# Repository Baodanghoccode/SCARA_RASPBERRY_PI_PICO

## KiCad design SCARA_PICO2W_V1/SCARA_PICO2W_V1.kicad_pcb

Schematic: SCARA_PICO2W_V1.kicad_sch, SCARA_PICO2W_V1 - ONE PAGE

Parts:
A201: Raspberry Pi Pico 2 W; RaspberryPi_Pico_Common_THT_AntennaWindow; MPN Raspberry Pi Pico 2 W
A401, A501, A601, A701: A4988 module; Pololu_Breakout-16_15.2x20.3mm_Socket_D1.02mm; MPN Nshop 6R08 A4988 module
C101: 470u 50V; CP_Radial_D12.5mm_P5.00mm; Voltage 50V; Tolerance 20%; MPN UPW1H471MHD
C102, C402, C502, C602, C702: 100n 50V; C_0805_2012Metric; Tolerance 10%; Voltage 50 V; MPN CC0805KRX7R9BB104
C103: 470u 25V LOW ESR; CP_Radial_D10.0mm_P5.00mm; MPN UPW1E471MPD
C104: 330u 35V LOW ESR; CP_Radial_D10.0mm_P5.00mm; MPN UPW1V331MPD
C105, C120, C121: 470u 50V LOW ESR; CP_Radial_D12.5mm_P5.00mm; MPN UPW1H471MHD
C106: 100n 50V X7R; C_0805_2012Metric; MPN 0805 100nF50V X7R +/-10%
C112: 10n 50V X7R; C_0805_2012Metric; MPN 0805 10nF50V X7R +/-10%
C122, C124, C125: 1u 50V X7R; C_0805_2012Metric; MPN 0805 1uF50V X7R +/-10%
C132: 27n 50V X7R; C_0805_2012Metric; MPN 0805 27nF50V X7R +/-10%
C401, C501, C601, C701: 100u 50V; CP_Radial_D8.0mm_P3.50mm; Voltage 50V; Tolerance 20%; MPN UPW1H101MPD
C403, C503, C603, C703, C801, C901, C902, C903, C904, C905: 100n 16V; C_0805_2012Metric; Tolerance 10%; Voltage 50 V; MPN CC0805KRX7R9BB104
C802, C803: 220u 25V; CP_Radial_D8.0mm_P3.50mm; MPN EEUFR1E221
D102: 1.5KE30CA / DNP; D_DO-201AD_P15.24mm_Horizontal; MPN 1.5KE30CA; not fitted
D103, D104: MBR20100CT; TO-220-3_Vertical; MPN MBR20100CT (manufacturer/lot verify)
D151: BZT52C12; D_SOD-123; MPN BZT52C12
D201: SS14-E3/61T; D_SMA; MPN SS14-E3/61T
F101: 6.3A / 125VDC; Fuse_Littelfuse-NANO2-451_453; MPN 045106.3MRL
J101: 24V IN; TerminalBlock_Phoenix_MKDS-1,5-2-5.08_1x02_P5.08mm_Horizont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; MPN 1715721
J201: EXPANSION; PinHeader_1x10_P2.54mm_Vertical; MPN M20-9991046
J401: AX1 MOTOR; PinHeader_1x04_P2.54mm_Vertical; MPN M20-9990446
J501: AX2 MOTOR; PinHeader_1x04_P2.54mm_Vertical; MPN M20-9990446
J601: AX3 MOTOR; PinHeader_1x04_P2.54mm_Vertical; MPN M20-9990446
J701: AX4 MOTOR; PinHeader_1x04_P2.54mm_Vertical; MPN M20-9990446
J801: SERVO1 MG996R; PinHeader_1x03_P2.54mm_Vertical; MPN M20-9990346
J802: SERVO2 MG996R; PinHeader_1x03_P2.54mm_Vertical; MPN M20-9990346
J901: HOME1 NC; JST_XH_B2B-XH-A_1x02_P2.50mm_Vertical; MPN B2B-XH-A(LF)(SN)
J902: HOME2 NC; JST_XH_B2B-XH-A_1x02_P2.50mm_Vertical; MPN B2B-XH-A(LF)(SN)
J903: HOME3 NC; JST_XH_B2B-XH-A_1x02_P2.50mm_Vertical; MPN B2B-XH-A(LF)(SN)
J904: HOME4 NC; JST_XH_B2B-XH-A_1x02_P2.50mm_Vertical; MPN B2B-XH-A(LF)(SN)
J905: STOP_SENSE NC; JST_XH_B2B-XH-A_1x02_P2.50mm_Vertical; MPN B2B-XH-A(LF)(SN)
JP401, JP501, JP601, JP701: MS1 OPEN=0; PinHeader_1x02_P2.54mm_Vertical; MPN M20-9990246
JP402, JP502, JP602, JP702: MS2 OPEN=0; PinHeader_1x02_P2.54mm_Vertical; MPN M20-9990246
JP403, JP503, JP603, JP703: MS3 OPEN=0; PinHeader_1x02_P2.54mm_Vertical; MPN M20-9990246
JP801: SERVO ARM (OPEN); PinHeader_1x02_P2.54mm_Vertical; MPN M20-9990246
L101: 100u / CDRH127; L_12x12mm_H8mm; MPN CDRH127-101 (local part; exact manufact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
L102: 47u / CXT B011307; L_Toroid_Vertical_D20_W10_P10_Wire1mm; MPN CXT B011307 (47uH 10A advertised)
Q151: IRF4905; TO-220-3_Vertical_Drill1.4mm; MPN IRF4905PbF
R105, R123: 3k3 1%; R_0805_2012Metric; MPN 0805 3k3 1% >=0.125W
R106: 1k 1%; R_0805_2012Metric; MPN 0805 1k 1% >=0.125W
R107: 75R 1%; R_0805_2012Metric; MPN 0805 75R 1% >=0.125W
R122: 12k 1%; R_0805_2012Metric; MPN 0805 12k 1% >=0.125W
R124: 560R 1%; R_0805_2012Metric; MPN 0805 560R 1% >=0.125W
R150: 2k2 1% / 0.25W; R_0805_2012Metric; MPN 0805 2.2k 1% 0.25W
R151: 100k 1%; R_0805_2012Metric; MPN 0805 100k 1%
R401, R402, R403, R404, R405, R406, R407, R501, R502, R503, R504, R505, R506, R507, R601, R602, R603, R604, R605, R606, R607, R701, R702, R703, R704, R705, R706, R707, R801, R802, R807: 10k; R_0805_2012Metric; Tolerance 1%; MPN RC0805FR-0710KL
R803, R804: 220R; R_0805_2012Metric; Tolerance 1%; MPN RC0805FR-07220RL
R805, R806: 100k; R_0805_2012Metric; Tolerance 1%; MPN RC0805FR-07100KL
R901, R903, R905, R907, R909: 4k7; R_0805_2012Metric; Tolerance 1%; MPN RC0805FR-074K7L
R902, R904, R906, R908, R910: 1k; R_0805_2012Metric; Tolerance 1%; MPN RC0805FR-071KL
TP101: +24V_MAIN; TestPoint_Pad_D2.0mm; MPN PCB_PAD_2MM_NO_ASSEMBLY
TP102: +5V_LOGIC; TestPoint_Pad_D2.0mm; MPN PCB_PAD_2MM_NO_ASSEMBLY
TP103: +6V_SERVO; TestPoint_Pad_D2.0mm; MPN PCB_PAD_2MM_NO_ASSEMBLY
TP104: VSYS; TestPoint_Pad_D2.0mm; MPN PCB_PAD_2MM_NO_ASSEMBLY
TP105: +3V3; TestPoint_Pad_D2.0mm; MPN PCB_PAD_2MM_NO_ASSEMBLY
TP106: GND; TestPoint_Pad_D2.0mm; MPN PCB_PAD_2MM_NO_ASSEMBLY
U101: LM2596S-ADJ; TO-263-5_TabPin3; MPN LM2596S-ADJ (manufacturer/lot verify)
U102: XL4015E1; TO-263-5_TabPin3; MPN XL4015E1
U801: SN74AHCT125PWR; TSSOP-14_4.4x5mm_P0.65mm; MPN SN74AHCT125PWR

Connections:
+3V3: A201.36 (3V3), A401.2 (VDD), A501.2 (VDD), A601.2 (VDD), A701.2 (VDD), C403.1, C503.1, C603.1, C703.1, J201.8, JP401.1, JP402.1, JP403.1, JP501.1, JP502.1, JP503.1, JP601.1, JP602.1, JP603.1, JP701.1, JP702.1, JP703.1, R403.1, R404.1, R503.1, R504.1, R603.1, R604.1, R703.1, R704.1, R901.1, R903.1, R905.1, R907.1, R909.1, TP105.1 (1_1)
+5V_LOGIC: C103.1, C112.1, C801.1, D201.2 (A), L101.2, R105.1, R807.1, TP102.1 (1_1), U801.10, U801.13, U801.14 (VCC)
+6V_SERVO: C104.1, C125.1, C132.1, C802.1, C803.1, J801.2, J802.2, L102.2, R122.1, TP103.1 (1_1)
+24V_MAIN: A401.8 (VMOT), A501.8 (VMOT), A601.8 (VMOT), A701.8 (VMOT), C101.1, C102.1, C105.1, C106.1, C120.1, C121.1, C122.1, C124.1, C401.1, C402.1, C501.1, C502.1, C601.1, C602.1, C701.1, C702.1, D102.1 (A1), D151.1 (K), Q151.3 (S), R151.1, TP101.1 (1_1), U101.1 (VIN), U102.5 (VIN)
/BUCK5_FB: C112.2, R105.2, R106.1, U101.4 (FB)
/BUCK5_SW: D103.2 (K), L101.1, U101.2 (OUT)
/BUCK6_FB: C132.2, R123.1, R124.2, U102.2 (FB)
/BUCK6_SW: D104.2 (K), L102.1, U102.3 (SW)
/RP_GATE: D151.2 (A), Q151.1 (G), R150.1, R151.2
AX1_1A: A401.4 (1A), J401.3
AX1_1B: A401.3 (1B), J401.4
AX1_2A: A401.5 (2A), J401.2
AX1_2B: A401.6 (2B), J401.1
AX1_DIR: A201.5 (GPIO3), A401.16 (DIR), R402.1
AX1_EN_N: A201.6 (GPIO4), A401.9 (~ENABLE), R403.2
AX1_MS1: A401.10 (MS1), JP401.2, R405.1
AX1_MS2: A401.11 (MS2), JP402.2, R406.1
AX1_MS3: A401.12 (MS3), JP403.2, R407.1
AX1_RSTSLP: A401.13 (~RESET), A401.14 (~SLEEP), R404.2
AX1_STEP: A201.4 (GPIO2), A401.15 (STEP), R401.1
AX2_1A: A501.4 (1A), J501.3
AX2_1B: A501.3 (1B), J501.4
AX2_2A: A501.5 (2A), J501.2
AX2_2B: A501.6 (2B), J501.1
AX2_DIR: A201.9 (GPIO6), A501.16 (DIR), R502.1
AX2_EN_N: A201.10 (GPIO7), A501.9 (~ENABLE), R503.2
AX2_MS1: A501.10 (MS1), JP501.2, R505.1
AX2_MS2: A501.11 (MS2), JP502.2, R506.1
AX2_MS3: A501.12 (MS3), JP503.2, R507.1
AX2_RSTSLP: A501.13 (~RESET), A501.14 (~SLEEP), R504.2
AX2_STEP: A201.7 (GPIO5), A501.15 (STEP), R501.1
AX3_1A: A601.4 (1A), J601.3
AX3_1B: A601.3 (1B), J601.4
AX3_2A: A601.5 (2A), J601.2
AX3_2B: A601.6 (2B), J601.1
AX3_DIR: A201.12 (GPIO9), A601.16 (DIR), R602.1
AX3_EN_N: A201.14 (GPIO10), A601.9 (~ENABLE), R603.2
AX3_MS1: A601.10 (MS1), JP601.2, R605.1
AX3_MS2: A601.11 (MS2), JP602.2, R606.1
AX3_MS3: A601.12 (MS3), JP603.2, R607.1
AX3_RSTSLP: A601.13 (~RESET), A601.14 (~SLEEP), R604.2
AX3_STEP: A201.11 (GPIO8), A601.15 (STEP), R601.1
AX4_1A: A701.4 (1A), J701.3
AX4_1B: A701.3 (1B), J701.4
AX4_2A: A701.5 (2A), J701.2
AX4_2B: A701.6 (2B), J701.1
AX4_DIR: A201.16 (GPIO12), A701.16 (DIR), R702.1
AX4_EN_N: A201.17 (GPIO13), A701.9 (~ENABLE), R703.2
AX4_MS1: A701.10 (MS1), JP701.2, R705.1
AX4_MS2: A701.11 (MS2), JP702.2, R706.1
AX4_MS3: A701.12 (MS3), JP703.2, R707.1
AX4_RSTSLP: A701.13 (~RESET), A701.14 (~SLEEP), R704.2
AX4_STEP: A201.15 (GPIO11), A701.15 (STEP), R701.1
EXP_GP0: A201.1 (GPIO0), J201.1
EXP_GP1: A201.2 (GPIO1), J201.2
EXP_GP21: A201.27 (GPIO21), J201.3
EXP_GP22: A201.29 (GPIO22), J201.4
EXP_GP26: A201.31 (GPIO26_ADC0), J201.5
EXP_GP27: A201.32 (GPIO27_ADC1), J201.6
EXP_GP28: A201.34 (GPIO28_ADC2), J201.7
GND: A201.3 (GND), A201.8 (GND), A201.13 (GND), A201.18 (GND), A201.23 (GND), A201.28 (GND), A201.33 (GND), A201.38 (GND), A401.1 (GND), A401.7 (GND), A501.1 (GND), A501.7 (GND), A601.1 (GND), A601.7 (GND), A701.1 (GND), A701.7 (GND), C101.2, C102.2, C103.2, C104.2, C105.2, C106.2, C120.2, C121.2, C122.2, C125.2, C401.2, C402.2, C403.2, C501.2, C502.2, C503.2, C601.2, C602.2, C603.2, C701.2, C702.2, C703.2, C801.2, C802.2, C803.2, C901.2, C902.2, C903.2, C904.2, C905.2, D102.2 (A2), D103.1 (A), D103.3 (A), D104.1 (A), D104.3 (A), J101.2, J201.9, J201.10, J801.1, J802.1, J901.2, J902.2, J903.2, J904.2, J905.2, JP801.1, R107.2, R123.2, R150.2, R401.2, R402.2, R405.2, R406.2, R407.2, R501.2, R502.2, R505.2, R506.2, R507.2, R601.2, R602.2, R605.2, R606.2, R607.2, R701.2, R702.2, R705.2, R706.2, R707.2, R801.2, R802.2, R805.2, R806.2, TP106.1 (1_1), U101.3 (GND), U101.5 (~ON/OFF), U102.1 (GND), U801.7 (GND), U801.9, U801.12
HOME1: A201.21 (GPIO16), C901.1, R902.2
HOME2: A201.22 (GPIO17), C902.1, R904.2
HOME3: A201.24 (GPIO18), C903.1, R906.2
HOME4: A201.25 (GPIO19), C904.1, R908.2
unnamed: F101.1, J101.1
unnamed: J901.1, R901.2, R902.1
unnamed: J902.1, R903.2, R904.1
unnamed: J903.1, R905.2, R906.1
unnamed: J904.1, R907.2, R908.1
unnamed: J905.1, R909.2, R910.1
unnamed: R106.2, R107.1
unnamed: R122.2, R124.1
unnamed: R803.1, U801.3
unnamed: R804.1, U801.6
unnamed: C124.2, U102.4 (VC)
SERVO1_PWM: A201.19 (GPIO14), R801.1, U801.2
SERVO1_SIGNAL: J801.3, R803.2, R805.1
SERVO2_PWM: A201.20 (GPIO15), R802.1, U801.5
SERVO2_SIGNAL: J802.3, R804.2, R806.1
SERVO_OE_N: JP801.2, R807.2, U801.1, U801.4
STOP_SENSE: A201.26 (GPIO20), C905.1, R910.2
V24_FUSED: F101.2, Q151.2 (D)
VSYS: A201.39 (VSYS), D201.1 (K), TP104.1 (1_1)

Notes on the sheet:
Cin: 2 × 470 µF/50 V; tổng dòng ripple ≥ 2,5 A RMS. Chọn Nichicon PW; đối chiếu hàng mua.
STOP_SENSE: chỉ đọc trạng thái. Cắt công suất và giữ trục Z: thiết kế riêng.
5 V / mục tiêu 1 A. Cần kiểm tra linh kiện, ESR, nhiệt và ngắn mạch.
SERVO / ĐỆM TÍN HIỆU 5 V
Tụ VC nối VIN. Tab U102 và D104 là SW6; phải cách điện với tản nhiệt GND.
NGUỒN SERVO / XL4015 / 6 V - MỤC TIÊU 5 A
Buck 6 V: khối bên phải
CHỌN VI BƯỚC / 4 TRỤC
Đầu ra danh định 6,008 V; không có biến trở. Đo trước khi cắm servo.
D102: KHÔNG LẮP. Kẹp tối đa 41,4 V, vượt giới hạn A4988 35 V.
Tụ 50 V không kẹp quá áp. Cần xử lý năng lượng động cơ trả về nguồn.
CÒN MỞ: quá áp, dòng nạp và năng lượng hồi về. Cần dữ liệu nguồn và tải cơ khí.
Lọc RC: lên ~570 µs, xuống ~100 µs; cần chống dội. STOP chỉ báo trạng thái, không cắt nguồn.
Bước chân 2,54 mm; hai hàng cách 12,70 mm; lỗ Ø0,80 mm.
Mặc định: STEP/DIR = LOW; driver tắt. RESET/SLEEP kéo HIGH qua 10k; kiểm tra module thực.
F101 6,3 A; Q151 chống đảo cực; D151 kẹp cổng 12 V. Mục tiêu dòng vào ≤ 4 A liên tục.
Chân 1: NC; chân 2: COM/GND. Đóng = LOW; mở/đứt dây = HIGH. Chỉ dùng tiếp điểm khô; không đưa 12/24 V vào cổng.
9 EN_N | 10 MS1 | 11 MS2 | 12 MS3 | 13 RESET_N | 14 SLEEP_N | 15 STEP | 16 DIR
Cout: 330 µF + 2 × 220 µF. Cff 27 nF: cần thử ổn định, vọt áp và khởi động đủ tải.
Giới hạn dòng: Imax = VREF / (8 × Rsense). Đo/đọc Rsense trên module trước khi chỉnh VREF.
GP26/27/28: tối đa 3,3 V; không cấp tín hiệu khi Pico mất nguồn.
XL4015: VIN 8–36 V; tối đa tuyệt đối 40 V. Toàn hệ vẫn cần VMOT < 35 V.
1 GND | 2 VDD | 3 1B | 4 1A | 5 2A | 6 2B | 7 GND | 8 VMOT
TRỤC 4 / MODULE A4988
A4988 / CHÂN CẮM VÀ ĐIỂM CẦN KIỂM TRA
VBUS40, RUN30, 3V3_EN37, ADC_VREF35 để hở. GND và AGND33 nối chung.
MS1/MS2/MS3: 000 = đủ bước; 100 = 1/2; 010 = 1/4; 110 = 1/8; 111 = 1/16. 1 = cắm jumper. Chỉ đổi khi động cơ dừng.
TRỤC 1 / MODULE A4988
Socket cái 2x1x8, P2,54; hai hàng 12,70 mm; lỗ Ø1,02 mm.
TRỤC 2 / MODULE A4988
3V3 tải ngoài < 300 mA; J201 ≤ 50 mA. Không cấp 6/24 V vào Pico hoặc nguồn ngoài vào VBUS.
NGUỒN LOGIC / LM2596 / 5 V - MỤC TIÊU 1 A
SERVO ARM: mặc định tháo jumper = tắt tín hiệu. TI AHCT125 chịu đầu vào khi mất nguồn. Cấp nguồn ngược qua servo: chưa kiểm chứng.
Mục tiêu 5 A liên tục: cần kiểm chứng trên PCB. Giới hạn 7 A của IC chỉ là điển hình.
Footprint đã chốt. Cần xác định Rsense, mạch RESET/SLEEP và dòng chạy liên tục.
TRỤC 3 / MODULE A4988
42HD4401S-23B: 1,5 A/pha; 1,6 Ω; 2,7 mH; 1,8°; 0,42 N·m (thông số người dùng). A4988 chạy 1,5 A liên tục, không quạt: cần thử nhiệt.
SCARA_PICO2W_V1 | 4 TRỤC ĐỘNG CƠ BƯỚC + 2 SERVO
A4988: mức tối đa 2 A không bảo đảm chạy liên tục 1,5 A/pha.
VREF = 8 × Igiới_hạn × Rsense. Không mặc định VREF = 0,6 V.

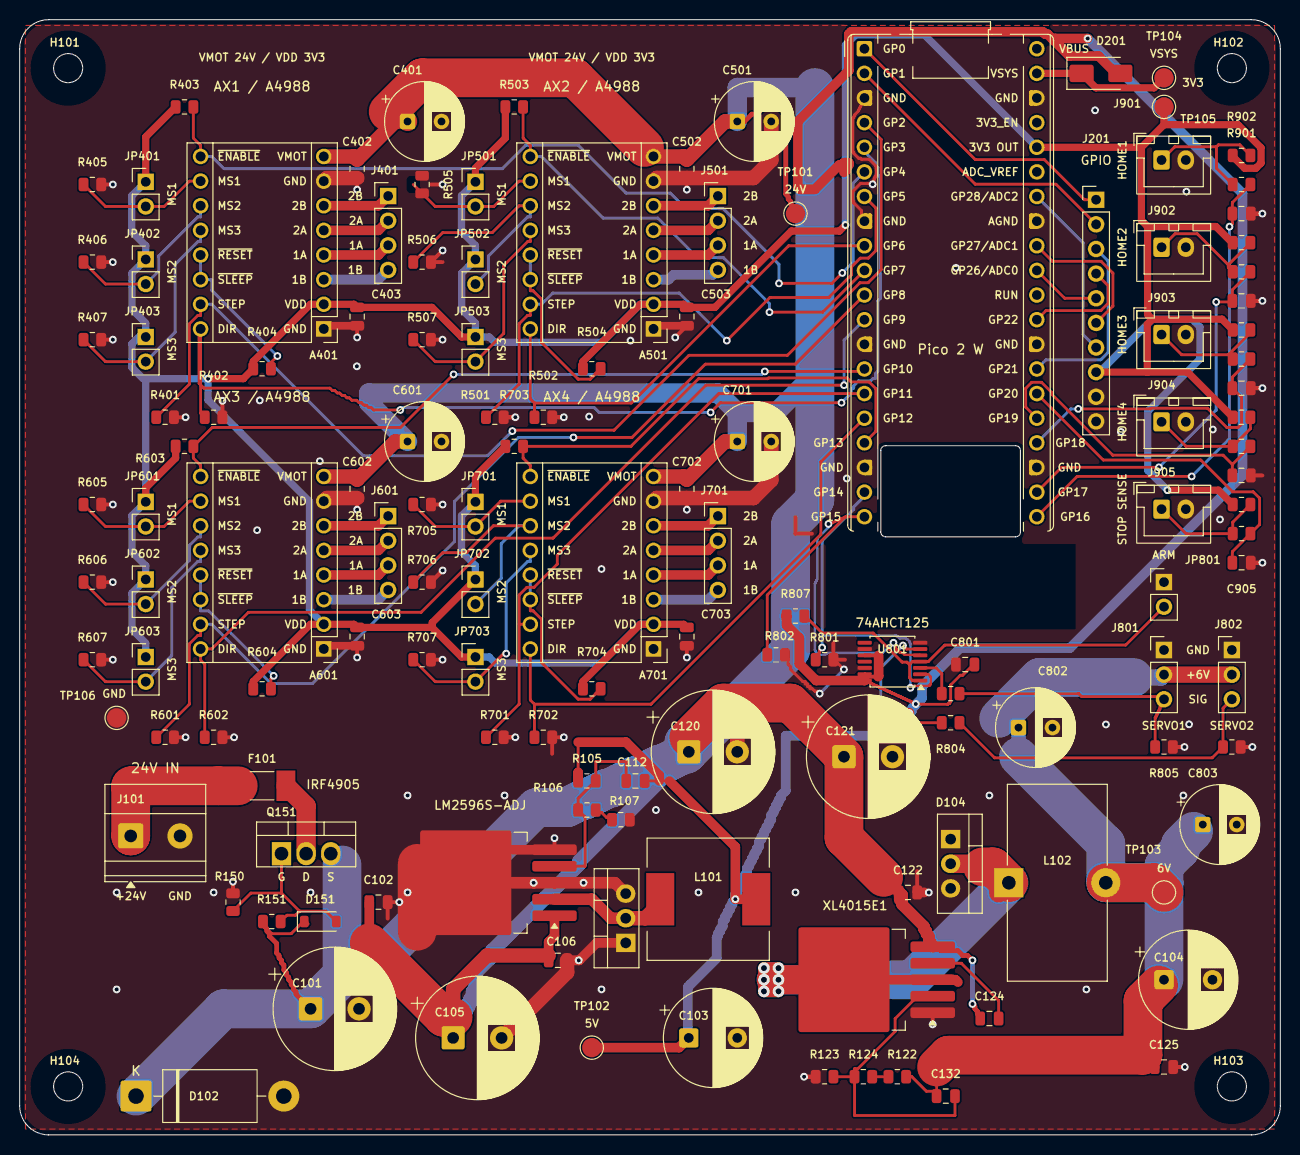
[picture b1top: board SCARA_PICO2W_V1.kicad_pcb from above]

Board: 2 copper layers, 130.0 x 115.0 mm, 139 parts (0 on the bottom side), 84 nets.

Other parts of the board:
H101, H102, H103, H104: D3.0 NPTH; MountingHole_3mm
